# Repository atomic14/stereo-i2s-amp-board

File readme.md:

# MAX98357 Stereo Amplifier Breakout Board

Click the image below to watch a video on the design of this breakout board:

# Overview

This is a version of the Adafruit MAX98537 amplifier board, but with stereo output. It uses two MAX98357 ICs, one for the left channel and one for the right channel.

The board should be pretty much the same size as the Adafruit board, but the mounting holes are slightly smaller due to lack of space.

Pin out is the same, but you will have to take the SD line high to enable the output. Taking the SD line low will put the ICs into low power mode.

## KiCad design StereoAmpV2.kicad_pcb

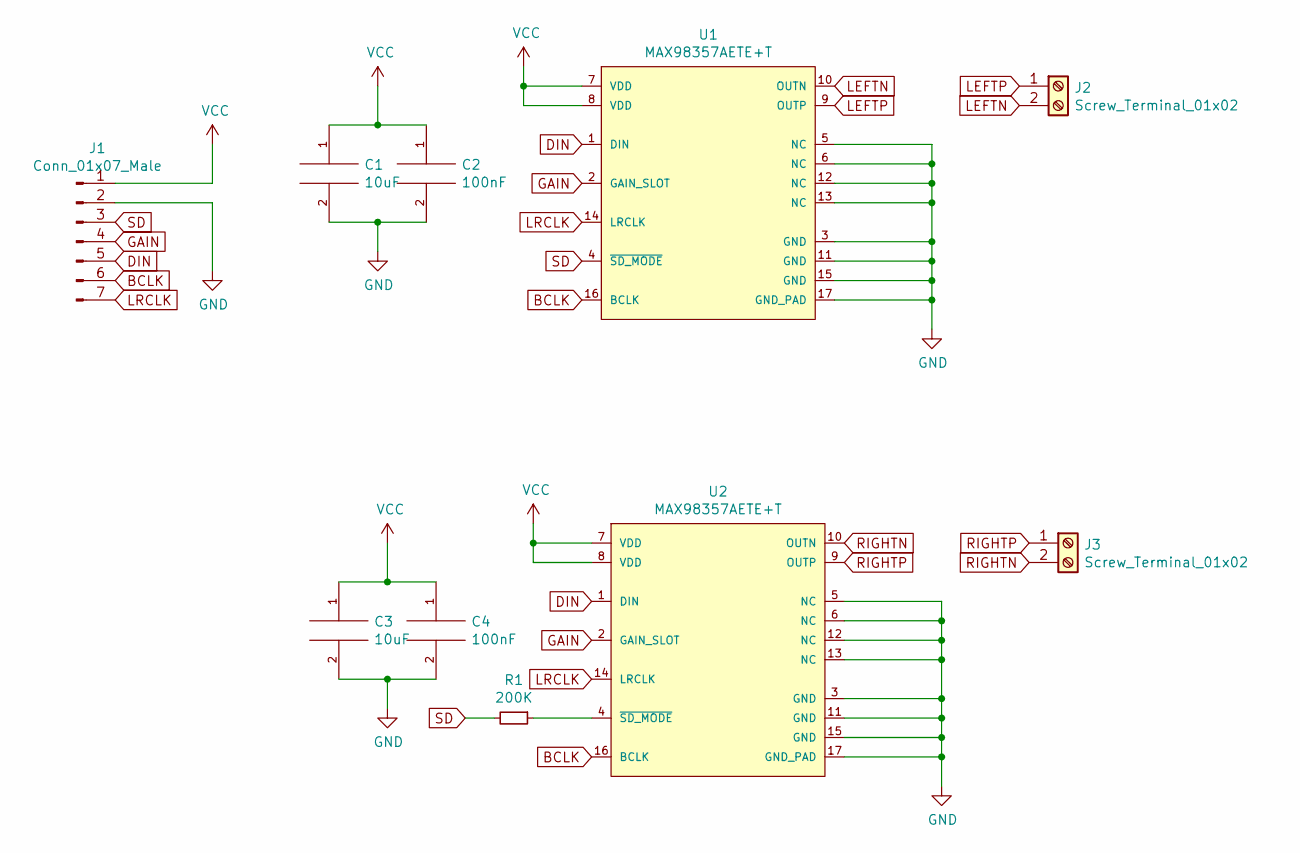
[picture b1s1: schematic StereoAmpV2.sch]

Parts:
C1, C3: 10uF; C_0402_1005Metric
C2, C4: 100nF; C_0402_1005Metric
J1: Conn_01x07_Male; PinHeader_1x07_P2.54mm_Vertical
J2, J3: Screw_Terminal_01x02; TerminalBlock_Phoenix_MPT-0,5-2-2.54_1x02_P2.54mm_Horizontal
R1: 200K; R_0402_1005Metric
U1, U2: MAX98357AETE+T; Maxim_Electronics-21-0896-0-0-0; mouser part number 700-MAX98357AETE+T; digikey description Amplifier IC 2-Channel (Stereo) Class D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

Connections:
BCLK: J1.6, U1.16 (BCLK), U2.16 (BCLK)
DIN: J1.5, U1.1 (DIN), U2.1 (DIN)
GAIN: J1.4, U1.2 (GAIN_SLOT), U2.2 (GAIN_SLOT)
GND: C1.2, C2.2, C3.2, C4.2, J1.2, U1.3 (GND), U1.5 (NC), U1.6 (NC), U1.11 (GND), U1.12 (NC), U1.13 (NC), U1.15 (GND), U1.17 (GND_PAD), U2.3 (GND), U2.5 (NC), U2.6 (NC), U2.11 (GND), U2.12 (NC), U2.13 (NC), U2.15 (GND), U2.17 (GND_PAD)
LEFTN: J2.2, U1.10 (OUTN)
LEFTP: J2.1, U1.9 (OUTP)
LRCLK: J1.7, U1.14 (LRCLK), U2.14 (LRCLK)
unnamed: R1.1, U2.4 (~SD_MODE~)
RIGHTN: J3.2, U2.10 (OUTN)
RIGHTP: J3.1, U2.9 (OUTP)
SD: J1.3, R1.2, U1.4 (~SD_MODE~)
VCC: C1.1, C2.1, C3.1, C4.1, J1.1, U1.7 (VDD), U1.8 (VDD), U2.7 (VDD), U2.8 (VDD)

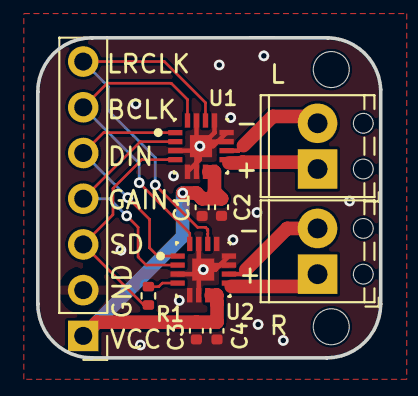
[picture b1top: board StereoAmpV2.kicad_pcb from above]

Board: 2 copper layers, 19.1 x 17.8 mm, 10 parts (0 on the bottom side), 12 nets.

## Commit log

2021-07-12 Adds some boxes and labels to schematic
